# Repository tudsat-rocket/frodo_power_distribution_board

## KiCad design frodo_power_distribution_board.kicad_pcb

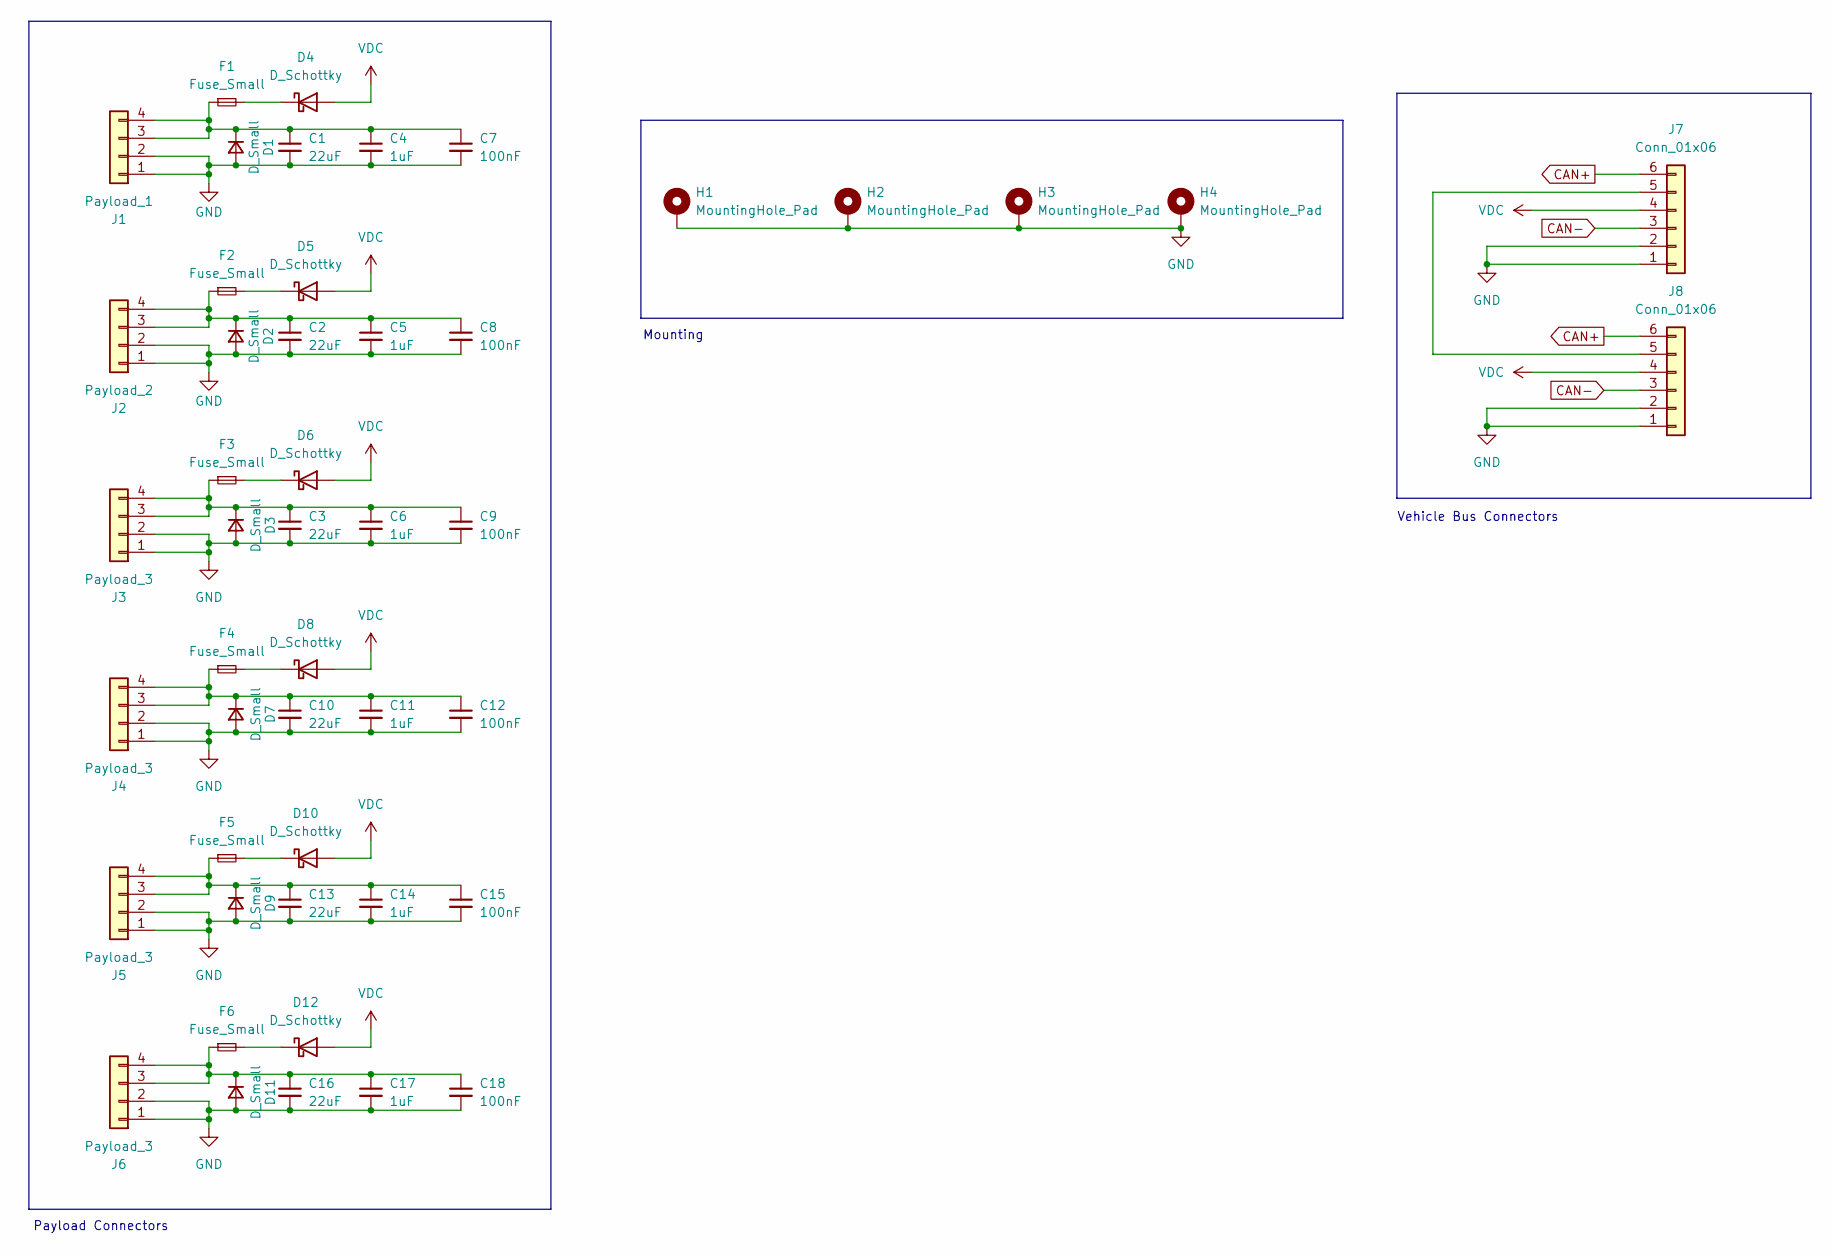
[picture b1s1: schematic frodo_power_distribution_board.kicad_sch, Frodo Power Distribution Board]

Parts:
C1, C2, C3, C10, C13, C16: 22uF; C_1206_3216Metric_Pad1.33x1.80mm_HandSolder
C4, C5, C6, C11, C14, C17: 1uF; C_0805_2012Metric_Pad1.18x1.45mm_HandSolder
C7, C8, C9, C12, C15, C18: 100nF; C_0603_1608Metric_Pad1.08x0.95mm_HandSolder
D1, D2, D3, D7, D9, D11: D_Small; D_SOD-123F
D4, D5, D6, D8, D10, D12: D_Schottky; D_SMA
F1, F2, F3, F4, F5, F6: Fuse_Small; Fuse_1206_3216Metric
H1, H2, H3, H4: MountingHole_Pad; MountingHole_3.2mm_M3_Pad_Via
J1: Payload_1; Molex_Micro-Fit_3.0_43045-0400_2x02_P3.00mm_Horizontal
J2: Payload_2; Molex_Micro-Fit_3.0_43045-0400_2x02_P3.00mm_Horizontal
J3, J4, J5, J6: Payload_3; Molex_Micro-Fit_3.0_43045-0400_2x02_P3.00mm_Horizontal
J7, J8: Conn_01x06; Molex_Micro-Fit_3.0_43045-0600_2x03_P3.00mm_Horizontal

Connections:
CAN+: J7.6, J8.6
CAN-: J7.3, J8.3
GND: C1.2, C2.2, C3.2, C4.2, C5.2, C6.2, C7.2, C8.2, C9.2, C10.2, C11.2, C12.2, C13.2, C14.2, C15.2, C16.2, C17.2, C18.2, D1.2 (A), D2.2 (A), D3.2 (A), D7.2 (A), D9.2 (A), D11.2 (A), H1.1, H2.1, H3.1, H4.1, J1.1, J1.2, J2.1, J2.2, J3.1, J3.2, J4.1, J4.2, J5.1, J5.2, J6.1, J6.2, J7.1, J7.2, J8.1, J8.2
unnamed: C1.1, C4.1, C7.1, D1.1 (K), F1.1, J1.3, J1.4
unnamed: C2.1, C5.1, C8.1, D2.1 (K), F2.1, J2.3, J2.4
unnamed: C3.1, C6.1, C9.1, D3.1 (K), F3.1, J3.3, J3.4
unnamed: D4.1 (K), F1.2
unnamed: D5.1 (K), F2.2
unnamed: D6.1 (K), F3.2
unnamed: C10.1, C11.1, C12.1, D7.1 (K), F4.1, J4.3, J4.4
unnamed: D8.1 (K), F4.2
unnamed: C13.1, C14.1, C15.1, D9.1 (K), F5.1, J5.3, J5.4
unnamed: D10.1 (K), F5.2
unnamed: C16.1, C17.1, C18.1, D11.1 (K), F6.1, J6.3, J6.4
unnamed: D12.1 (K), F6.2
unnamed: J7.5, J8.5
VDC: D4.2 (A), D5.2 (A), D6.2 (A), D8.2 (A), D10.2 (A), D12.2 (A), J7.4, J8.4

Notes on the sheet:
Vehicle Bus Connectors
Payload Connectors
Mounting

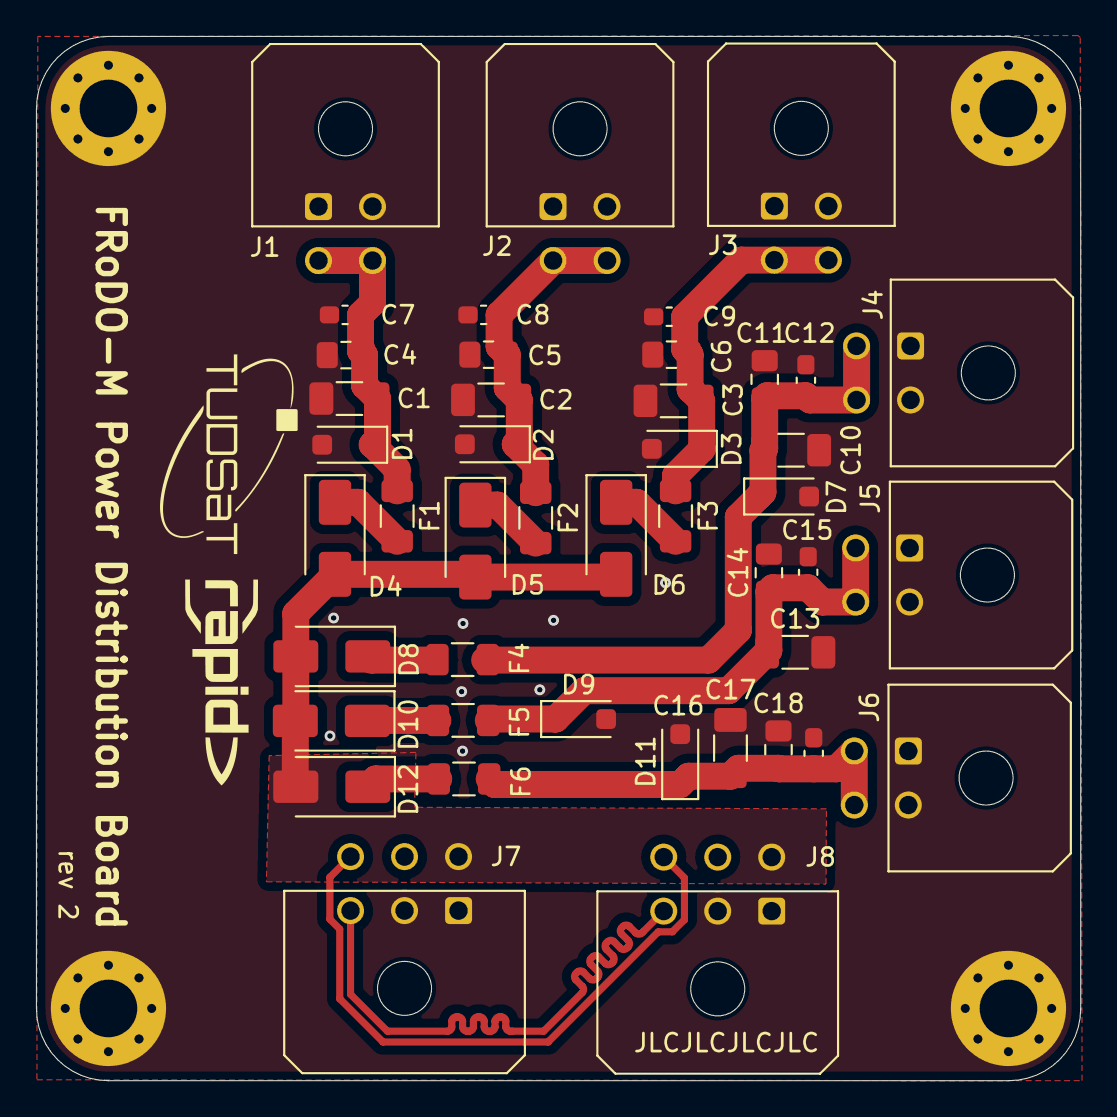
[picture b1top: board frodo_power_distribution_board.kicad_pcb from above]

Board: 2 copper layers, 58.0 x 58.0 mm, 48 parts (0 on the bottom side), 17 nets.

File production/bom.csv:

Designator,Footprint,Quantity,Value,LCSC Part #
"C1, C10, C13, C16, C2, C3",1206,6,22uF,
"C11, C14, C17, C4, C5, C6",0805,6,1uF,
"C12, C15, C18, C7, C8, C9",0603,6,100nF,
"D1, D11, D2, D3, D7, D9",D_SOD-123F,6,D_Small,
"D10, D12, D4, D5, D6, D8",D_SMA,6,D_Schottky,
"F1, F2, F3, F4, F5, F6",1206,6,Fuse_Small,
"H1, H2, H3, H4",MountingHole_3.2mm_M3_Pad_Via,4,MountingHole_Pad,
J1,Molex_Micro-Fit_3.0_43045-0400_2x02_P3.00mm_Horizontal,1,Payload_1,
J2,Molex_Micro-Fit_3.0_43045-0400_2x02_P3.00mm_Horizontal,1,Payload_2,
"J3, J4, J5, J6",Molex_Micro-Fit_3.0_43045-0400_2x02_P3.00mm_Horizontal,4,Payload_3,
"J7, J8",Molex_Micro-Fit_3.0_43045-0600_2x03_P3.00mm_Horizontal,2,Conn_01x06,

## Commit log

2024-05-20 Specify board schematics
2024-06-24 First iteration of board layout
2024-06-24 Add missing connection
2024-06-26 Round off edges, skew CAN, widen traces
2024-06-29 Fatten traces, remove thermal relief, fix 2x2 pinout, move filter components inline
2024-07-01 Make pretty
2024-07-04 Refill zones for Gerber export
2024-07-08 add 3d models of Molex connectors
2024-07-28 Increase number of charge bus connectors to six
2024-07-28 Remove accidentally commited lock files
2024-07-31 Rev2
